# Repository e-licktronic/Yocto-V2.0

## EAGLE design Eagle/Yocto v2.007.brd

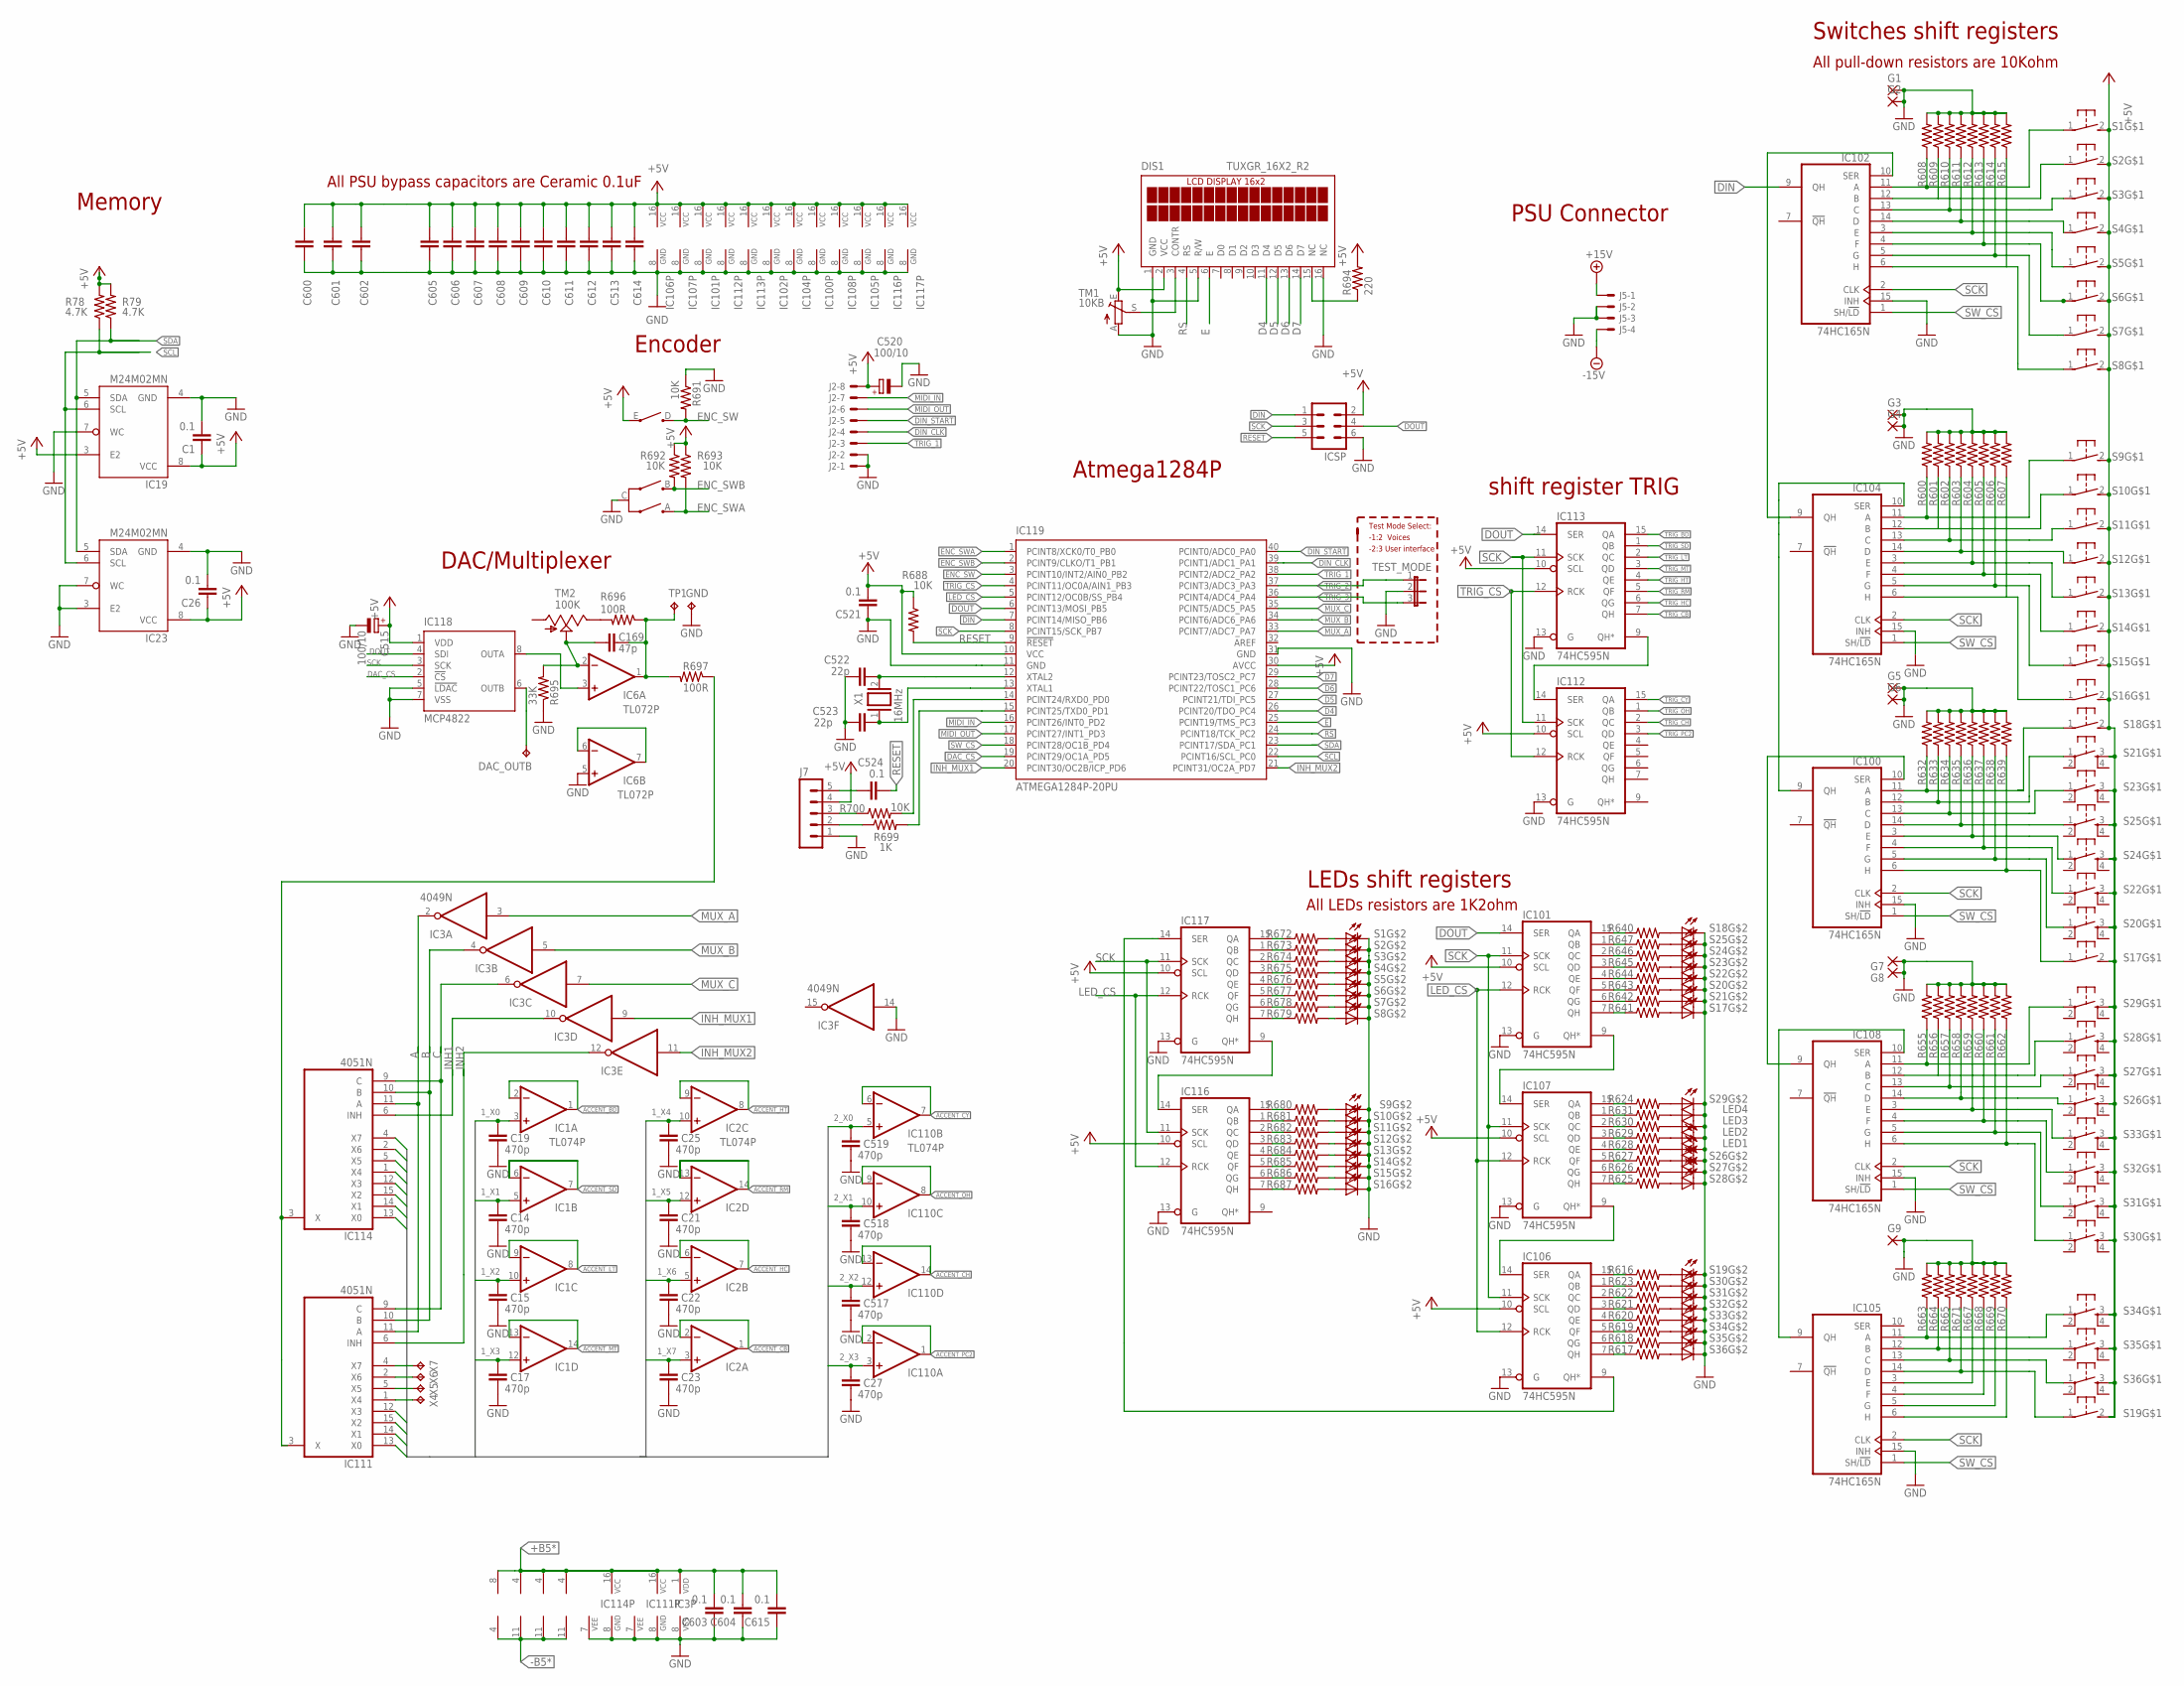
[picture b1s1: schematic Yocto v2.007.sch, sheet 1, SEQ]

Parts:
C1, C26, C513, C521, C524, C600, C601, C602, C603, C604, C605, C606, C607, C608, C609, C610, C611, C612, C614, C615: 0.1; C050-024X044
C14, C15, C17, C19, C21, C22, C23, C25, C27, C517, C518, C519: 470p; C050-025X075
C169: 47p; C025-025X050
C515, C520: 100/10; E2-5
C522, C523: 22p; C025-025X050
DAC_OUTB: TPB0,8; B0,8
DIS1: TUXGR_16X2_R2
G1, G2, G3, G4, G5, G6, G7, G8, G9: WIREPAD1,6/0,8; 1,6/0,8
GND: TPB0,8; B0,8
IC1, IC2, IC110: TL074P; DIL14
IC3: 4049N; DIL16
IC6: TL072P; DIL08
IC19, IC23: M24M02MN; SO08
IC100, IC102, IC104, IC105, IC108: 74HC165N; DIL16
IC101, IC106, IC107, IC112, IC113, IC116, IC117: 74HC595N; DIL16
IC111, IC114: 4051N; DIL16
IC118: MCP4822; DIL8
IC119: ATMEGA1284P-20PU; DIL40
ICSP: MA03-2
J2: 22-27-2081-08; 6410-08
J5: KK-156-4
J7: MA05-1; MA05-1A
LED1, LED2, LED3, LED4: LED3MM
R78, R79: 4.7K; 0207/7
R600, R601, R602, R603, R604, R605, R606, R607, R608, R609, R610, R611, R612, R613, R614, R615, R632, R633, R634, R635, R636, R637, R638, R639, R655, R656, R657, R658, R659, R660, R661, R662, R663, R664, R665, R667, R668, R669, R670, R671, R688, R691, R692, R693, R700: 10K; 0207/7
R616, R617, R618, R619, R620, R621, R622, R623, R624, R625, R626, R627, R628, R629, R630, R631, R640, R641, R642, R643, R644, R645, R646, R647, R672, R673, R674, R675, R676, R677, R678, R679, R680, R681, R682, R683, R684, R685, R686, R687: 1.2K; 0207/7
R694: 220; 0207/7
R695: 33K; 0207/7
R696, R697: 100R; 0207/7
R699: 1K; 0207/7
S1, S2, S3, S4, S5, S6, S7, S8, S9, S10, S11, S12, S13, S14, S15, S16, S17, S18, S19: MX1A_CHERRY_SW_LED"; MX1A-SW
S20, S21, S22, S23, S24, S25, S26, S27, S28, S29, S30, S31, S32, S33, S34, S35, S36: ZTSN_SW_LED"; SPH_SW
TEST_MODE: JP2E; JP2
TM1: 10KB; CT6
TM2: 100K; S64W
TP1: TPB0,8; B0,8
VR29: PEC16_ENCODER
X1: 16MHz; QS
X4, X5, X6, X7: TPB0,8; B0,8

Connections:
1_X0: C19.1, IC1.3 (+IN), IC114.13 (X0)
1_X1: C14.1, IC1.5 (+IN), IC114.14 (X1)
1_X2: C15.1, IC1.10 (+IN), IC114.15 (X2)
1_X3: C17.1, IC1.12 (+IN), IC114.12 (X3)
1_X4: C25.1, IC2.10 (+IN), IC114.1 (X4)
1_X5: C21.1, IC2.12 (+IN), IC114.5 (X5)
1_X6: C22.1, IC2.5 (+IN), IC114.2 (X6)
1_X7: C23.1, IC2.3 (+IN), IC114.4 (X7)
2_X0: C519.1, IC110.5 (+IN), IC111.13 (X0)
2_X1: C518.1, IC110.10 (+IN), IC111.14 (X1)
2_X2: C517.1, IC110.12 (+IN), IC111.15 (X2)
2_X3: C27.1, IC110.3 (+IN), IC111.12 (X3)
+5V: C1.1, C26.1, C513.2, C515.+, C520.+, C521.2, C600.2, C601.2, C602.2, C605.2, C606.2, C607.2, C608.2, C609.2, C610.2, C611.2, C612.2, C614.2, DIS1.2 (VCC), IC19.3 (E2), IC19.8 (VCC), IC23.8 (VCC), IC100.16 (VCC), IC101.10 (SCL), IC101.16 (VCC), IC102.16 (VCC), IC104.16 (VCC), IC105.16 (VCC), IC106.10 (SCL), IC106.16 (VCC), IC107.10 (SCL), IC107.16 (VCC), IC108.16 (VCC), IC112.10 (SCL), IC112.16 (VCC), IC113.10 (SCL), IC113.16 (VCC), IC116.10 (SCL), IC116.16 (VCC), IC117.10 (SCL), IC117.16 (VCC), IC118.1 (VDD), IC119.10 (VCC), IC119.30 (AVCC), ICSP.2, J2.8, J7.4, R78.2, R79.2, R688.1, R692.1, R693.1, R694.2, S1.2 (S), S2.2 (S), S3.2 (S), S4.2 (S), S5.2 (S), S6.2 (S), S7.2 (S), S8.2 (S), S9.2 (S), S10.2 (S), S11.2 (S), S12.2 (S), S13.2 (S), S14.2 (S), S15.2 (S), S16.2 (S), S17.2 (S), S18.2 (S), S19.2 (S), S20.3 (S), S21.3 (S), S22.3 (S), S23.3 (S), S24.3 (S), S25.3 (S), S26.3 (S), S27.3 (S), S28.3 (S), S29.3 (S), S30.3 (S), S31.3 (S), S32.3 (S), S33.3 (S), S34.3 (S), S35.3 (S), S36.3 (S), TM1.E, VR29.E; also elsewhere on the board
+15V: J5.1; also elsewhere on the board
+B5*: C603.2, C604.2, C615.2, IC1.4 (V+), IC2.4 (V+), IC3.1 (VDD), IC6.8 (V+), IC110.4 (V+), IC111.16 (VCC), IC114.16 (VCC); also elsewhere on the board
-15V: J5.4; also elsewhere on the board
-B5*: IC1.11 (V-), IC2.11 (V-), IC6.4 (V-), IC110.11 (V-); also elsewhere on the board
A: IC3.2 (O), IC111.11 (A), IC114.11 (A)
ACCENT_BD: IC1.1 (OUT), IC1.2 (-IN); also elsewhere on the board
ACCENT_CB: IC2.1 (OUT), IC2.2 (-IN); also elsewhere on the board
ACCENT_CH: IC110.13 (-IN), IC110.14 (OUT); also elsewhere on the board
ACCENT_CY: IC110.6 (-IN), IC110.7 (OUT); also elsewhere on the board
ACCENT_HC: IC2.6 (-IN), IC2.7 (OUT); also elsewhere on the board
ACCENT_HT: IC2.8 (OUT), IC2.9 (-IN); also elsewhere on the board
ACCENT_LT: IC1.8 (OUT), IC1.9 (-IN); also elsewhere on the board
ACCENT_MT: IC1.13 (-IN), IC1.14 (OUT); also elsewhere on the board
ACCENT_OH: IC110.8 (OUT), IC110.9 (-IN); also elsewhere on the board
ACCENT_PC2: IC110.1 (OUT), IC110.2 (-IN); also elsewhere on the board
ACCENT_RM: IC2.13 (-IN), IC2.14 (OUT); also elsewhere on the board
ACCENT_SD: IC1.6 (-IN), IC1.7 (OUT); also elsewhere on the board
B: IC3.4 (O), IC111.10 (B), IC114.10 (B)
C: IC3.6 (O), IC111.9 (C), IC114.9 (C)
D4: DIS1.11 (D4), IC119.26 (PCINT20/TDO_PC4)
D5: DIS1.12 (D5), IC119.27 (PCINT21/TDI_PC5)
D6: DIS1.13 (D6), IC119.28 (PCINT22/TOSC1_PC6)
D7: DIS1.14 (D7), IC119.29 (PCINT23/TOSC2_PC7)
DAC_CS: IC118.2 (!CS!), IC119.19 (PCINT29/OC1A_PD5)
DIN: IC102.9 (QH), IC119.7 (PCINT14/MISO_PB6), ICSP.1
DIN_CLK: IC119.39 (PCINT1/ADC1_PA1), J2.4
DIN_START: IC119.40 (PCINT0/ADC0_PA0), J2.5
DOUT: IC101.14 (SER), IC113.14 (SER), IC118.4 (SDI), IC119.6 (PCINT13/MOSI_PB5), ICSP.4
E: DIS1.6 (E), IC119.25 (PCINT19/TMS_PC3)
ENC_SW: IC119.3 (PCINT10/INT2/AIN0_PB2), R691.2, VR29.D
ENC_SWA: IC119.1 (PCINT8/XCK0/T0_PB0), R693.2, VR29.A
ENC_SWB: IC119.2 (PCINT9/CLKO/T1_PB1), R692.2, VR29.B
GND: C1.2, C14.2, C15.2, C17.2, C19.2, C21.2, C22.2, C23.2, C25.2, C26.2, C27.2, C513.1, C515.-, C517.2, C518.2, C519.2, C520.-, C521.1, C522.1, C523.1, C600.1, C601.1, C602.1, C603.1, C604.1, C605.1, C606.1, C607.1, C608.1, C609.1, C610.1, C611.1, C612.1, C614.1, C615.1, DIS1.1 (GND), DIS1.5 (R/W), DIS1.16 (NC), G1.1, G2.1, G3.1, G4.1, G5.1, G6.1, G7.1, G8.1, G9.1, GND.P$1, IC3.8 (VSS), IC3.14 (I), IC6.5 (+IN), IC19.4 (GND), IC19.7 (WC), IC23.3 (E2), IC23.4 (GND), IC23.7 (WC), IC100.8 (GND), IC100.15 (INH), IC101.8 (GND), IC101.13 (G), IC102.8 (GND), IC102.15 (INH), IC104.8 (GND), IC104.15 (INH), IC105.8 (GND), IC105.15 (INH), IC106.8 (GND), IC106.13 (G), IC107.8 (GND), IC107.13 (G), IC108.8 (GND), IC108.15 (INH), IC111.7 (VEE), IC111.8 (GND), IC112.8 (GND), IC112.13 (G), IC113.8 (GND), IC113.13 (G), IC114.7 (VEE), IC114.8 (GND), IC116.8 (GND), IC116.13 (G), IC117.8 (GND), IC117.13 (G), IC118.5 (!LDAC!), IC118.7 (VSS), IC119.11 (GND), IC119.31 (GND), ICSP.6, J2.1, J2.2, J5.2, J5.3, J7.1, LED1.K (C), LED2.K (C), LED3.K (C), LED4.K (C), R600.2, R601.2, R602.2, R603.2, R604.2, R605.2, R606.2, R607.2, R608.2, R609.2, R610.2, R611.2, R612.2, R613.2, R614.2, R615.2, R632.2, R633.2, R634.2, R635.2, R636.2, R637.2, R638.2, R639.2, R655.2, R656.2, R657.2, R658.2, R659.2, R660.2, R661.2, R662.2, R663.2, R664.2, R665.2, R667.2, R668.2, R669.2, R670.2, R671.2, R691.1, R695.1, S1.K (C), S2.K (C), S3.K (C), S4.K (C), S5.K (C), S6.K (C), S7.K (C), S8.K (C), S9.K (C), S10.K (C), S11.K (C), S12.K (C), S13.K (C), S14.K (C), S15.K (C), S16.K (C), S17.K (C), S18.K (C), S19.K (C), S20.K (C), S21.K (C), S22.K (C), S23.K (C), S24.K (C), S25.K (C), S26.K (C), S27.K (C), S28.K (C), S29.K (C), S30.K (C), S31.K (C), S32.K (C), S33.K (C), S34.K (C), S35.K (C), S36.K (C), TEST_MODE.2, TM1.A, VR29.C; also elsewhere on the board
INH1: IC3.10 (O), IC114.6 (INH)
INH2: IC3.12 (O), IC111.6 (INH)
INH_MUX1: IC3.9 (I), IC119.20 (PCINT30/OC2B/ICP_PD6)
INH_MUX2: IC3.11 (I), IC119.21 (PCINT31/OC2A_PD7)
LED_CS: IC101.12 (RCK), IC106.12 (RCK), IC107.12 (RCK), IC116.12 (RCK), IC117.12 (RCK), IC119.5 (PCINT12/OC0B/SS_PB4)
MIDI_IN: IC119.16 (PCINT26/INT0_PD2), J2.7
MIDI_OUT: IC119.17 (PCINT27/INT1_PD3), J2.6
MUX_A: IC3.3 (I), IC119.33 (PCINT7/ADC7_PA7)
MUX_B: IC3.5 (I), IC119.34 (PCINT6/ADC6_PA6)
MUX_C: IC3.7 (I), IC119.35 (PCINT5/ADC5_PA5)
unnamed: R624.2, S29.A
unnamed: R625.2, S28.A
unnamed: R626.2, S27.A
unnamed: R627.2, S26.A
unnamed: R647.2, S25.A
unnamed: R646.2, S24.A
unnamed: R645.2, S23.A
unnamed: R644.2, S22.A
unnamed: R642.2, S21.A
unnamed: R643.2, S20.A
unnamed: R640.2, S18.A
unnamed: R641.2, S17.A
unnamed: LED4.A, R631.2
unnamed: LED3.A, R630.2
unnamed: LED2.A, R629.2
unnamed: LED1.A, R628.2
unnamed: R616.2, S19.A
unnamed: R617.2, S36.A
unnamed: R618.2, S35.A
unnamed: R619.2, S34.A
unnamed: R620.2, S33.A
unnamed: R621.2, S32.A
unnamed: R622.2, S31.A
unnamed: R623.2, S30.A
unnamed: IC108.14 (D), R658.1, S26.1
unnamed: IC6.3 (+IN), IC118.8 (OUTA)
unnamed: IC117.15 (QA), R672.1
unnamed: IC117.1 (QB), R673.1
unnamed: IC117.2 (QC), R674.1
unnamed: IC117.3 (QD), R675.1
unnamed: IC117.4 (QE), R676.1
unnamed: IC117.5 (QF), R677.1
unnamed: IC117.6 (QG), R678.1
unnamed: IC117.7 (QH), R679.1
unnamed: IC116.14 (SER), IC117.9 (QH*)
unnamed: IC116.15 (QA), R680.1
unnamed: IC116.1 (QB), R681.1
unnamed: IC116.2 (QC), R682.1
unnamed: IC116.3 (QD), R683.1
unnamed: IC116.4 (QE), R684.1
unnamed: IC116.5 (QF), R685.1
unnamed: IC116.6 (QG), R686.1
unnamed: IC116.7 (QH), R687.1
unnamed: R680.2, S9.A
unnamed: R681.2, S10.A
unnamed: R682.2, S11.A
unnamed: R683.2, S12.A
unnamed: R684.2, S13.A
unnamed: R685.2, S14.A
unnamed: R686.2, S15.A
unnamed: R687.2, S16.A
unnamed: R672.2, S1.A
unnamed: R673.2, S2.A
unnamed: R674.2, S3.A
unnamed: R675.2, S4.A
unnamed: R676.2, S5.A
unnamed: R677.2, S6.A
unnamed: R678.2, S7.A
unnamed: R679.2, S8.A
unnamed: IC106.9 (QH*), IC117.14 (SER)
unnamed: IC6.6 (-IN), IC6.7 (OUT)
unnamed: IC119.15 (PCINT25/TXD0_PD1), R699.2
unnamed: IC119.14 (PCINT24/RXD0_PD0), R700.2
unnamed: IC112.14 (SER), IC113.9 (QH*)
unnamed: C522.2, IC119.12 (XTAL2), X1.2
unnamed: C523.2, IC119.13 (XTAL1), X1.1
unnamed: IC111.1 (X4), X4.P$1
unnamed: IC111.5 (X5), X5.P$1
unnamed: IC111.2 (X6), X6.P$1
unnamed: IC111.4 (X7), X7.P$1
unnamed: IC102.11 (A), R608.1, S1.1
unnamed: IC102.12 (B), R609.1, S2.1
unnamed: IC102.13 (C), R610.1, S3.1
unnamed: IC102.14 (D), R611.1, S4.1
unnamed: IC102.3 (E), R612.1, S5.1
unnamed: IC102.4 (F), R613.1, S6.1
unnamed: IC102.5 (G), R614.1, S7.1
unnamed: IC102.6 (H), R615.1, S8.1
unnamed: IC104.11 (A), R600.1, S9.1
unnamed: IC104.12 (B), R601.1, S10.1
unnamed: IC104.13 (C), R602.1, S11.1
unnamed: IC104.14 (D), R603.1, S12.1
unnamed: IC104.3 (E), R604.1, S13.1
unnamed: IC104.4 (F), R605.1, S14.1
unnamed: IC104.5 (G), R606.1, S15.1
unnamed: IC104.6 (H), R607.1, S16.1
unnamed: IC100.11 (A), R632.1, S18.1
unnamed: IC100.12 (B), R633.1, S21.1
unnamed: IC100.13 (C), R634.1, S23.1
unnamed: IC100.14 (D), R635.1, S25.1
unnamed: IC100.3 (E), R636.1, S24.1
unnamed: IC100.4 (F), R637.1, S22.1
unnamed: IC100.5 (G), R638.1, S20.1
unnamed: IC102.10 (SER), IC104.9 (QH)
unnamed: IC100.9 (QH), IC104.10 (SER)
unnamed: IC100.6 (H), R639.1, S17.1
unnamed: IC111.3 (X), IC114.3 (X), R697.1
unnamed: IC101.15 (QA), R640.1
unnamed: IC100.10 (SER), IC108.9 (QH)
unnamed: IC108.11 (A), R655.1, S29.1
unnamed: IC108.12 (B), R656.1, S28.1
unnamed: IC108.13 (C), R657.1, S27.1
unnamed: IC108.3 (E), R659.1, S33.1
unnamed: IC108.4 (F), R660.1, S32.1
unnamed: IC108.5 (G), R661.1, S31.1
unnamed: IC108.6 (H), R662.1, S30.1
unnamed: IC101.1 (QB), R647.1
unnamed: IC105.9 (QH), IC108.10 (SER)
unnamed: IC101.2 (QC), R646.1
unnamed: IC105.11 (A), R663.1, S34.1
unnamed: IC105.12 (B), R664.1, S35.1
unnamed: IC105.13 (C), R665.1, S36.1
unnamed: IC105.14 (D), R671.1, S19.1
unnamed: IC105.3 (E), R667.1
unnamed: IC105.4 (F), R668.1
unnamed: IC105.5 (G), R669.1
unnamed: IC105.6 (H), R670.1
unnamed: IC101.3 (QD), R645.1
unnamed: IC101.4 (QE), R644.1
unnamed: IC101.5 (QF), R643.1
unnamed: IC101.6 (QG), R642.1
unnamed: IC101.7 (QH), R641.1
unnamed: IC107.15 (QA), R624.1
unnamed: IC107.1 (QB), R631.1
unnamed: IC107.2 (QC), R630.1
unnamed: IC107.3 (QD), R629.1
unnamed: IC107.4 (QE), R628.1
unnamed: IC107.5 (QF), R627.1
unnamed: IC107.6 (QG), R626.1
unnamed: IC107.7 (QH), R625.1
unnamed: IC101.9 (QH*), IC107.14 (SER)
unnamed: IC106.14 (SER), IC107.9 (QH*)
unnamed: IC106.15 (QA), R616.1
unnamed: IC106.1 (QB), R623.1
unnamed: IC106.2 (QC), R622.1
unnamed: IC106.3 (QD), R621.1
unnamed: IC106.4 (QE), R620.1
unnamed: IC106.5 (QF), R619.1
unnamed: IC106.6 (QG), R618.1
unnamed: IC106.7 (QH), R617.1
unnamed: R696.2, TM2.E
unnamed: C169.2, IC6.1 (OUT), R696.1, R697.2, TP1.P$1
unnamed: C169.1, IC6.2 (-IN), R695.2, TM2.S
unnamed: DIS1.15 (NC), R694.1
unnamed: DIS1.3 (CONTR), TM1.S
unnamed: C524.2, J7.5
unnamed: J7.3, R700.1
unnamed: J7.2, R699.1
RESET: C524.1, IC119.9 (!RESET), ICSP.5, R688.2
RS: DIS1.4 (RS), IC119.24 (PCINT18/TCK_PC2)
SCK: IC100.2 (CLK), IC101.11 (SCK), IC102.2 (CLK), IC104.2 (CLK), IC105.2 (CLK), IC106.11 (SCK), IC107.11 (SCK), IC108.2 (CLK), IC112.11 (SCK), IC113.11 (SCK), IC116.11 (SCK), IC117.11 (SCK), IC118.3 (SCK), IC119.8 (PCINT15/SCK_PB7), ICSP.3
SCL: IC19.6 (SCL), IC23.6 (SCL), IC119.22 (PCINT16/SCL_PC0), R78.1
SDA: IC19.5 (SDA), IC23.5 (SDA), IC119.23 (PCINT17/SDA_PC1), R79.1
SW_CS: IC100.1 (SH/!LD), IC102.1 (SH/!LD), IC104.1 (SH/!LD), IC105.1 (SH/!LD), IC108.1 (SH/!LD), IC119.18 (PCINT28/OC1B_PD4)
TRIG_1: IC119.38 (PCINT2/ADC2_PA2), J2.3
TRIG_2: IC119.37 (PCINT3/ADC3_PA3), TEST_MODE.1
TRIG_3: IC119.36 (PCINT4/ADC4_PA4), TEST_MODE.3
TRIG_BD: IC113.15 (QA); also elsewhere on the board
TRIG_CB: IC113.7 (QH); also elsewhere on the board
TRIG_CH: IC112.2 (QC); also elsewhere on the board
TRIG_CS: IC112.12 (RCK), IC113.12 (RCK), IC119.4 (PCINT11/OC0A/AIN1_PB3)
TRIG_CY: IC112.15 (QA); also elsewhere on the board
TRIG_HC: IC113.6 (QG); also elsewhere on the board
TRIG_HT: IC113.4 (QE); also elsewhere on the board
TRIG_LT: IC113.2 (QC); also elsewhere on the board
TRIG_MT: IC113.3 (QD); also elsewhere on the board
TRIG_OH: IC112.1 (QB); also elsewhere on the board
TRIG_PC2: IC112.3 (QD); also elsewhere on the board
TRIG_RM: IC113.5 (QF); also elsewhere on the board
TRIG_SD: IC113.1 (QB); also elsewhere on the board
WN1: DAC_OUTB.P$1, IC118.6 (OUTB)

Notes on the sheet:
Memory
Encoder
Atmega1284P
DAC/Multiplexer
LEDs shift registers
shift register TRIG
Switches shift registers
PSU Connector
All pull-down resistors are 10Kohm
All PSU bypass capacitors are Ceramic 0.1uF
All LEDs resistors are 1K2ohm
Test Mode Select:
-1:2 Voices
-2:3 User interface

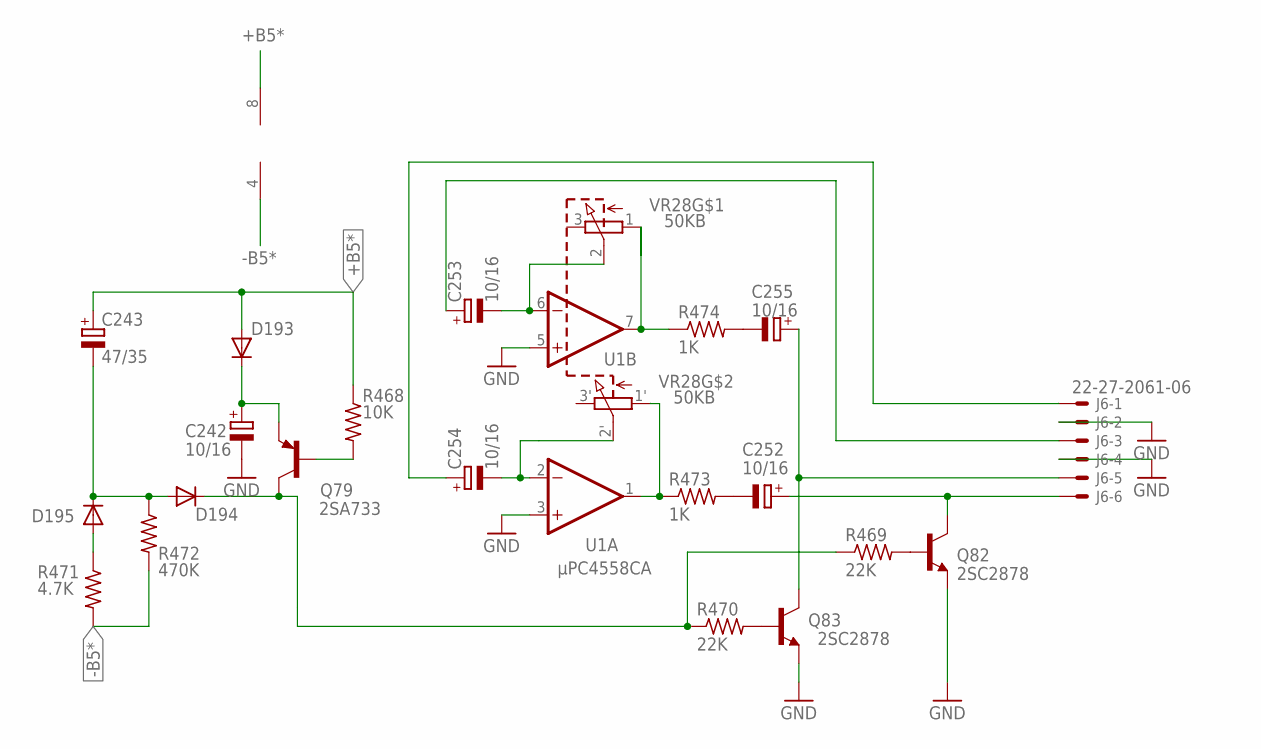
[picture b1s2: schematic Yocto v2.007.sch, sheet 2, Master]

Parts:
C242, C252, C253, C254, C255: 10/16; E2-5
C243: 47/35; E2,5-6
D193, D194, D195: 1N4148; DO35-7C
J6: 22-27-2061-06; 6410-06
Q79: 2SA733; TO-92-ECB-MARKED
Q82, Q83: 2SC2878; TO92-ECB
R468: 10K; 0207/7
R469, R470: 22K; 0207/7
R471: 4.7K; 0207/7
R472: 470K; 0207/7
R473, R474: 1K; 0207/7
U1: µPC4558CA; DIL08
VR28: 50KB; PTV112-4

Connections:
+B5*: C243.+, D193.A, R468.1, U1.8 (V+); also elsewhere on the board
-B5*: R471.2, R472.2, U1.4 (V-); also elsewhere on the board
GND: C242.-, J6.2, J6.4, Q82.E, Q83.E, U1.3 (+IN), U1.5 (+IN); also elsewhere on the board
unnamed: D195.A, R471.1
unnamed: C243.-, D194.A, D195.C, R472.1
unnamed: R474.1, U1.7 (OUT), VR28.1
unnamed: R473.1, U1.1 (OUT), VR28.1' (1)
unnamed: D194.C, Q79.C, R469.1, R470.1
unnamed: C242.+, D193.C, Q79.E
unnamed: Q79.B, R468.2
unnamed: C254.-, U1.2 (-IN), VR28.2' (2)
unnamed: C253.-, U1.6 (-IN), VR28.2
unnamed: C255.-, R474.2
unnamed: C252.-, R473.2
unnamed: Q82.B, R469.2
unnamed: Q83.B, R470.2
unnamed: C253.+, J6.3
unnamed: C255.+, J6.5, Q83.C
unnamed: C252.+, J6.6, Q82.C
unnamed: C254.+, J6.1

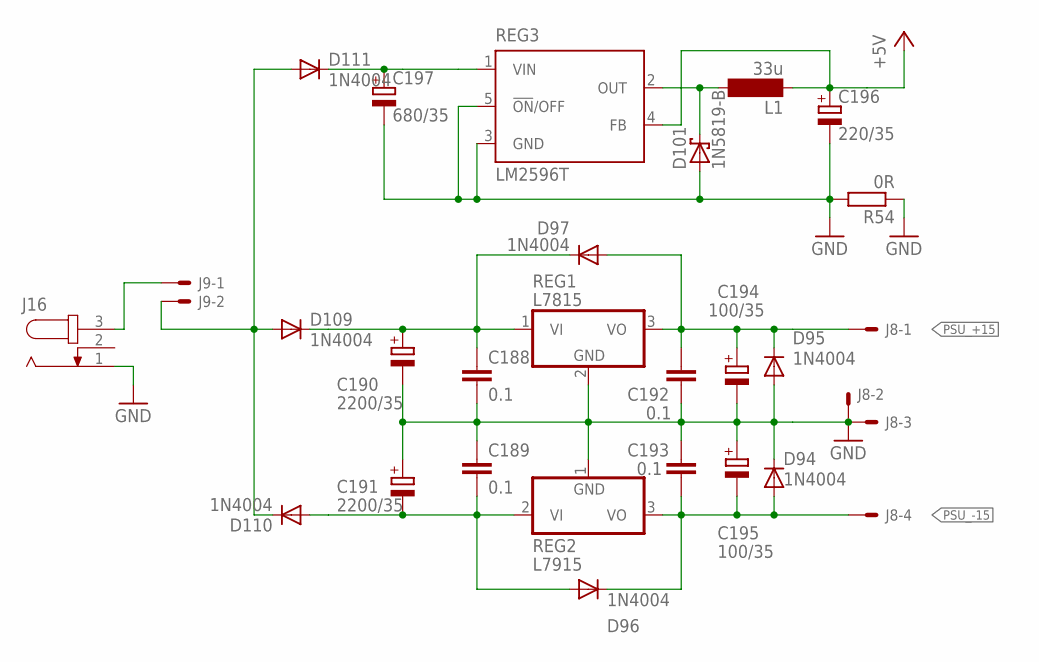
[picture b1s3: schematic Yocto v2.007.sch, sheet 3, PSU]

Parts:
C188, C189, C192, C193: 0.1; C050-024X044
C190, C191: 2200/35; E7,5-16
C194, C195: 100/35; E3,5-8
C196: 220/35; E3,5-8
C197: 680/35; E5-13
D94, D95, D96, D97, D109, D110, D111: 1N4004; DO41-7
D101: 1N5819-B; DO41-7.6
J8: KK-156-4
J9: KK-156-2
J16: JACK-PLUG0; JACK_PSU_2.1MM
L1: 33u; BS11
R54: 0R; 0207/7
REG1: L7815; TO220V
REG2: L7915; TO220V
REG3: LM2596T; T05D

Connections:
+5V: C196.+, L1.1, REG3.4 (FB); also elsewhere on the board
GND: C188.2, C189.1, C190.-, C191.+, C192.2, C193.1, C194.-, C195.+, C196.-, C197.-, D94.C, D95.A, D101.A, J8.2, J8.3, J16.1, R54.1, R54.2, REG1.2 (GND), REG2.1 (GND), REG3.3 (GND), REG3.5 (!ON!/OFF); also elsewhere on the board
unnamed: C189.2, C191.-, D96.A, D110.A, REG2.2 (VI)
unnamed: C188.1, C190.+, D97.C, D109.C, REG1.1 (VI)
unnamed: D109.A, D110.C, D111.A, J9.2
unnamed: C197.+, D111.C, REG3.1 (VIN)
unnamed: D101.C, L1.2, REG3.2 (OUT)
unnamed: J9.1, J16.3
PSU_+15: C192.1, C194.+, D95.C, D97.A, J8.1, REG1.3 (VO); also elsewhere on the board
PSU_-15: C193.2, C195.-, D94.A, D96.C, J8.4, REG2.3 (VO); also elsewhere on the board

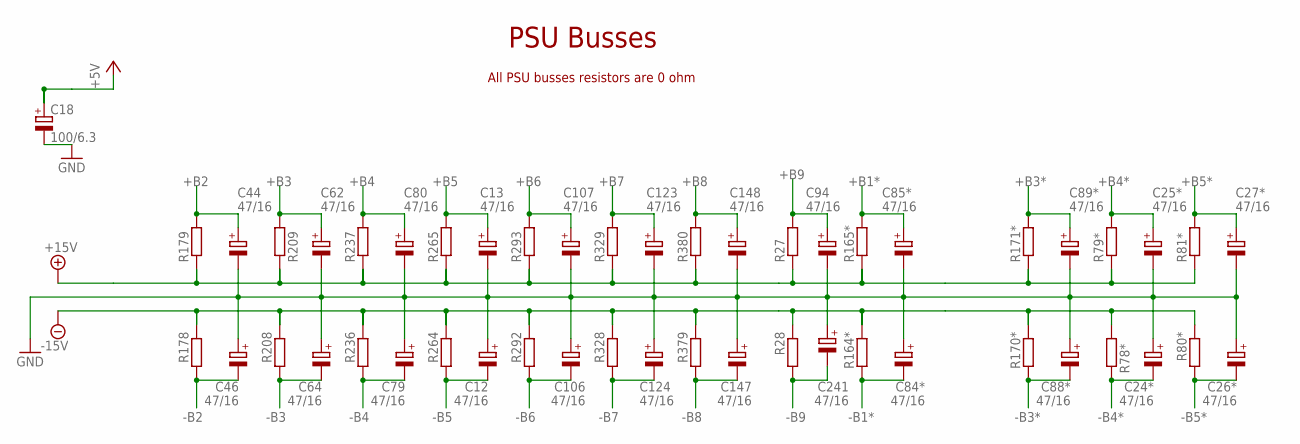
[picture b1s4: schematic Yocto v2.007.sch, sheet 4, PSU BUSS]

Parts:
C12, C13, C24*, C25*, C26*, C27*, C44, C46, C62, C64, C79, C80, C84*, C85*, C88*, C89*, C94, C106, C107, C123, C124, C147, C148, C241: 47/16; E2,5-6
C18: 100/6.3; E2-5
R27, R28, R78*, R79*, R80*, R81*, R164*, R165*, R170*, R171*, R178, R179, R208, R209, R236, R237, R264, R265, R292, R293, R328, R329, R379, R380: 0R; 0207/7

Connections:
+5V: C18.+; also elsewhere on the board
+15V: R27.1, R79*.1, R81*.1, R165*.1, R171*.1, R179.1, R209.1, R237.1, R265.1, R293.1, R329.1, R380.1; also elsewhere on the board
+B1*: C85*.+, R165*.2; also elsewhere on the board
+B2: C44.+, R179.2; also elsewhere on the board
+B3: C62.+, R209.2; also elsewhere on the board
+B3*: C89*.+, R171*.2; also elsewhere on the board
+B4: C80.+, R237.2; also elsewhere on the board
+B4*: C25*.+, R79*.2; also elsewhere on the board
+B5: C13.+, R265.2; also elsewhere on the board
+B5*: C27*.+, R81*.2; also elsewhere on the board
+B6: C107.+, R293.2; also elsewhere on the board
+B7: C123.+, R329.2; also elsewhere on the board
+B8: C148.+, R380.2; also elsewhere on the board
+B9: C94.+, R27.2; also elsewhere on the board
-15V: R28.1, R78*.2, R80*.1, R164*.1, R170*.1, R178.1, R208.1, R236.1, R264.1, R292.1, R328.1, R379.1; also elsewhere on the board
-B1*: C84*.-, R164*.2; also elsewhere on the board
-B2: C46.-, R178.2; also elsewhere on the board
-B3: C64.-, R208.2; also elsewhere on the board
-B3*: C88*.-, R170*.2; also elsewhere on the board
-B4: C79.-, R236.2; also elsewhere on the board
-B4*: C24*.-, R78*.1; also elsewhere on the board
-B5: C12.-, R264.2; also elsewhere on the board
-B5*: C26*.-, R80*.2; also elsewhere on the board
-B6: C106.-, R292.2; also elsewhere on the board
-B7: C124.-, R328.2; also elsewhere on the board
-B8: C147.-, R379.2; also elsewhere on the board
-B9: C241.-, R28.2; also elsewhere on the board
GND: C12.+, C13.-, C18.-, C24*.+, C25*.-, C26*.+, C27*.-, C44.-, C46.+, C62.-, C64.+, C79.+, C80.-, C84*.+, C85*.-, C88*.+, C89*.-, C94.-, C106.+, C107.-, C123.-, C124.+, C147.+, C148.-, C241.+; also elsewhere on the board

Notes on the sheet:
PSU Busses
All PSU busses resistors are 0 ohm

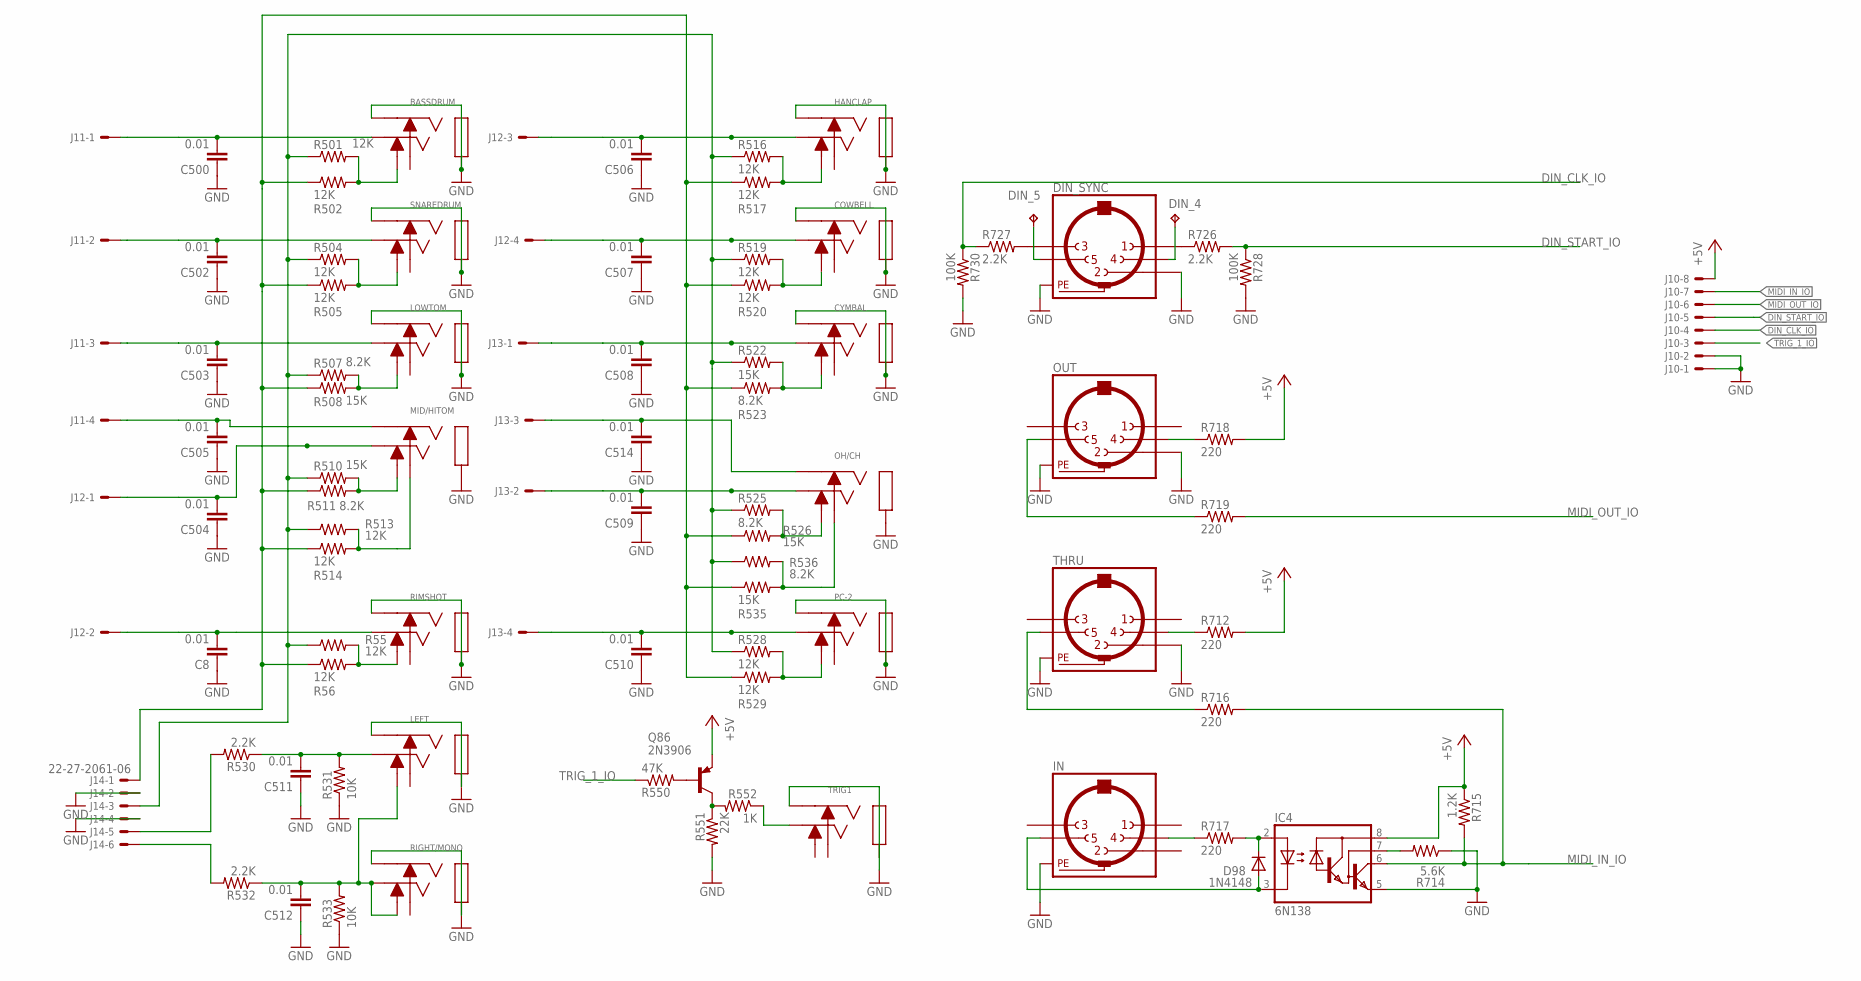
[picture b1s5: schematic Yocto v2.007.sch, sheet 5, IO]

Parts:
BASSDRUM: JACK_TRSNRJ6HF; JACK_TRS
C8, C500, C502, C503, C504, C505, C506, C507, C508, C509, C510, C511, C512, C514: 0.01; C050-025X075
COWBELL: JACK_TRSNRJ6HF; JACK_TRS
CYMBAL: JACK_TRSNRJ6HF; JACK_TRS
D98: 1N4148; DO35-7C
DIN_4, DIN_5: TPB0,8; B0,8
DIN_SYNC: MAB5SH
HANCLAP: JACK_TRSNRJ6HF; JACK_TRS
IC4: 6N138; DIL08
IN: MAB5SH
J10: 22-27-2081-08; 6410-08
J11, J12, J13: 22-27-2041-04; 6410-04
J14: 22-27-2061-06; 6410-06
LEFT: JACK_TRSNRJ6HF; JACK_TRS
LOWTOM: JACK_TRSNRJ6HF; JACK_TRS
MID/HITOM: JACK_TRSNRJ6HF; JACK_TRS
OH/CH: JACK_TRSNRJ6HF; JACK_TRS
OUT: MAB5SH
PC-2: JACK_TRSNRJ6HF; JACK_TRS
Q86: 2N3906; TO92-EBC-SMALL
R55, R56, R501, R502, R504, R505, R513, R514, R516, R517, R519, R520, R528, R529: 12K; 0207/7
R507, R511, R523, R525, R536: 8.2K; 0207/7
R508, R510, R522, R526, R535: 15K; 0207/7
R530, R532, R726, R727: 2.2K; 0207/7
R531, R533: 10K; 0207/7
R550: 47K; 0207/7
R551: 22K; 0207/7
R552: 1K; 0207/7
R712, R716, R717, R718, R719: 220; 0207/7
R714: 5.6K; 0207/7
R715: 1.2K; 0207/7
R728, R730: 100K; 0207/7
RIGHT/MONO: JACK_TRSNRJ6HF; JACK_TRS
RIMSHOT: JACK_TRSNRJ6HF; JACK_TRS
SNAREDRUM: JACK_TRSNRJ6HF; JACK_TRS
THRU: MAB5SH
TRIG1: JACK_TRSNRJ6HF; JACK_TRS

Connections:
+5V: IC4.8 (VCC), J10.8, Q86.E, R712.2, R715.1, R718.2; also elsewhere on the board
DIN_CLK_IO: J10.4, R727.1, R730.1
DIN_START_IO: J10.5, R726.2, R728.1
GND: BASSDRUM.R, BASSDRUM.S, C8.1, C500.1, C502.1, C503.1, C504.1, C505.1, C506.1, C507.1, C508.1, C509.1, C510.1, C511.1, C512.1, C514.1, COWBELL.R, COWBELL.S, CYMBAL.R, CYMBAL.S, DIN_SYNC.2, DIN_SYNC.PE, DIN_SYNC.PE@ (PE), HANCLAP.R, HANCLAP.S, IC4.5 (GND), IN.PE, IN.PE@ (PE), J10.1, J10.2, J14.2, J14.4, LEFT.R, LEFT.S, LOWTOM.R, LOWTOM.S, MID/HITOM.S, OH/CH.S, OUT.2, OUT.PE, OUT.PE@ (PE), PC-2.R, PC-2.S, R531.1, R533.1, R551.2, R714.1, R728.2, R730.2, RIGHT/MONO.R, RIGHT/MONO.S, RIMSHOT.R, RIMSHOT.S, SNAREDRUM.R, SNAREDRUM.S, THRU.2, THRU.PE, THRU.PE@ (PE), TRIG1.R, TRIG1.S; also elsewhere on the board
MIDI_IN_IO: IC4.6 (VO), J10.7, R715.2, R716.2
MIDI_OUT_IO: J10.6, R719.2
unnamed: R552.1, TRIG1.T
unnamed: R55.2, R56.2, RIMSHOT.TN
unnamed: C8.2, J12.2, RIMSHOT.T
unnamed: OH/CH.RN, R535.2, R536.2
unnamed: C514.2, J13.3, OH/CH.R
unnamed: DIN_5.P$1, DIN_SYNC.5
unnamed: DIN_4.P$1, DIN_SYNC.4
unnamed: BASSDRUM.TN, R501.2, R502.2
unnamed: BASSDRUM.T, C500.2, J11.1
unnamed: Q86.B, R550.2
unnamed: C512.2, LEFT.TN, R532.1, R533.2, RIGHT/MONO.T, RIGHT/MONO.TN
unnamed: R504.2, R505.2, SNAREDRUM.TN
unnamed: C502.2, J11.2, SNAREDRUM.T
unnamed: C511.2, LEFT.T, R530.1, R531.2
unnamed: LOWTOM.TN, R507.2, R508.2
unnamed: C503.2, J11.3, LOWTOM.T
unnamed: MID/HITOM.TN, R510.2, R511.2
unnamed: C504.2, J12.1, MID/HITOM.T
unnamed: MID/HITOM.RN, R513.2, R514.2
unnamed: C505.2, J11.4, MID/HITOM.R
unnamed: J14.1, R56.1, R502.1, R505.1, R508.1, R511.1, R514.1, R517.1, R520.1, R523.1, R526.1, R529.1, R535.1
unnamed: HANCLAP.TN, R516.2, R517.2
unnamed: C506.2, HANCLAP.T, J12.3
unnamed: COWBELL.TN, R519.2, R520.2
unnamed: IN.4, R717.1
unnamed: D98.C, IC4.2 (A), R717.2
unnamed: D98.A, IC4.3 (C), IN.5
unnamed: R712.1, THRU.4
unnamed: R716.1, THRU.5
unnamed: IC4.7 (VB), R714.2
unnamed: OUT.4, R718.1
unnamed: OUT.5, R719.1
unnamed: DIN_SYNC.1, R726.1
unnamed: DIN_SYNC.3, R727.2
unnamed: C507.2, COWBELL.T, J12.4
unnamed: Q86.C, R551.1, R552.2
unnamed: CYMBAL.TN, R522.2, R523.2
unnamed: C508.2, CYMBAL.T, J13.1
unnamed: J14.5, R530.2
unnamed: J14.6, R532.2
unnamed: OH/CH.TN, R525.2, R526.2
unnamed: C509.2, J13.2, OH/CH.T
unnamed: PC-2.TN, R528.2, R529.2
unnamed: C510.2, J13.4, PC-2.T
unnamed: J14.3, R55.1, R501.1, R504.1, R507.1, R510.1, R513.1, R516.1, R519.1, R522.1, R525.1, R528.1, R536.1
TRIG_1_IO: J10.3, R550.1

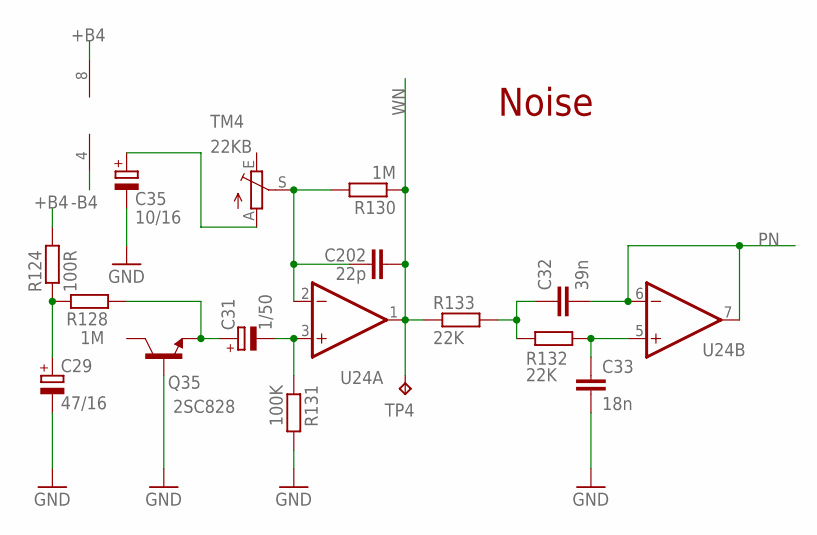
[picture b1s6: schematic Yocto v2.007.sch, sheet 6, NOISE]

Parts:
C29: 47/16; E2,5-6
C31: 1/50; E2-5
C32: 39n; C050-025X075
C33: 18n; C050-025X075
C35: 10/16; E2-5
C202: 22p; C025-025X050
Q35: 2SC828; TO-ECB-MARKED2
R124: 100R; 0207/7
R128, R130: 1M; 0207/7
R131: 100K; 0207/7
R132, R133: 22K; 0207/7
TM4: 22KB; CT6
TP4: TPB0,8; B0,8
U24: µPC4558CA; DIL08

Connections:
+B4: R124.2, U24.8 (V+); also elsewhere on the board
-B4: U24.4 (V-); also elsewhere on the board
GND: C29.-, C33.2, C35.-, Q35.B, R131.2; also elsewhere on the board
unnamed: C35.+, TM4.A
unnamed: C31.-, R131.1, U24.3 (+IN)
unnamed: C202.1, R130.2, TM4.S, U24.2 (-IN)
unnamed: C31.+, Q35.E, R128.1
unnamed: C29.+, R124.1, R128.2
unnamed: C32.1, R132.1, R133.2
unnamed: C33.1, R132.2, U24.5 (+IN)
PN: C32.2, U24.6 (-IN), U24.7 (OUT); also elsewhere on the board
WN: C202.2, R130.1, R133.1, TP4.P$1, U24.1 (OUT); also elsewhere on the board

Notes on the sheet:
Noise
